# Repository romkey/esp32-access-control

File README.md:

# esp32-access-control

An open source, ESP32-based Wiegand reader: a board, ESPHome firmware and a 3D-printable case.

At PDX Hackerspace we used RFID keys to unlock doors and access our laser cutter. We want to expand their use, to make it easy for members to print parking permits for projects, unlock the main entrance for events, claim prints on 3D printers and more. We currently use Raspberry Pis for the doors and an ESPKey for the laser cutter; this project can provide a low cost simple way to integrate with Wiegand RFID readers and possibly as the basis for replacing the aging Raspberry Pis controlling our doors.

> **AI disclosure:** This project was written by AI under human oversight,
> following [these rules](https://github.com/romkey/esphome-ai-coding-rules/blob/main/RULES.md).

## What's here

| Path | What it is |
|------|------------|
| `hw/reader/<version>/` | KiCad project for the board, one directory per revision |
| `BOFFF.md` | Bill of Form, Fit and Function: board outline, mounting holes and connector positions, for designing enclosures |
| `examples/access-control.yaml` | The door controller: Wiegand reader, access database, door relay, syslog |
| `examples/simple.yaml` | ESPHome config for bring-up: LED switch, reader LED and beeper, Wiegand tag reading |
| `examples/common/base.yaml` | Settings every example shares: encrypted API and OTA, recovery, web server |
| `packages/` | Board-agnostic ESPHome packages for the door controller; pins come from the including config |
| `components/` | C++ external components: `access_db`, `access_site`, `access_syslog`, `push_auth` |
| `case/` | OpenSCAD design for a wall or desk kiosk in portrait and landscape layouts; see [case/README.md](case/README.md) |
| `datasheets/` | Manufacturer datasheets, each with a license note |
| `docs/` | [Overview](docs/overview.md) and [configuration reference](docs/configuration.md) |

## Technical details

Hardware:

- dual level-shifted 5V Wiegand interfaces with wiring for data (D0, D1), LED and beep along with power
- ESP32-S3-N16R8: ESP32-S3 with 16MB of flash and 8MB of octal PSRAM (GPIO35-37 are used by the PSRAM and unavailable)
- USB C port
- power and data LEDs
- Qwiic connector for I2C devices
- header for SPI TFT displays with touch controllers
- "aux" header for satellite boards with optional power to this board

Connectors, from [BOFFF.md](BOFFF.md):

| Ref | Part | What it is |
|-----|------|------------|
| J1 | 10-pin header | Aux: GND, 3.3V, TX0, RX0, IO42, IO41, IO40, IO39, IO38, +5V in |
| J2 | 14-pin header | SPI TFT with touch: 3.3V, GND, CS, RST, DC, SDO, SCK, LED, SDI, then T_CLK, T_CS, T_DIN, T_DO, T_IRQ |
| J3 | SM04B-SRSS-TB | Qwiic: GND, 3.3V, SDA, SCL |
| J4 | USB-C | Power and programming |
| J5, J6 | WAGO 2601-1106 | Wiegand readers 1 and 2: +5V, GND, then four signals (D0, D1, LED, beep; see the schematic for the order) |

I2C: SDA and SCL on J3, with 4.7k pull-ups to 3.3V. The board carries no I2C devices of its own.

`examples/simple.yaml` and `examples/access-control.yaml` wire one reader on D0 = GPIO18, D1 = GPIO17, reader LED = GPIO16
(active low) and beeper = GPIO15 (active low). Check these against the schematic before
relying on them. The board has no relay output; `packages/door-relays.yaml` is an example for a relay or strike driven from
the J1 aux header or a satellite board. `examples/access-control.yaml` uses GPIO38 and GPIO39 (J1) as example
values; set `door_relay_1_pin` and `door_relay_2_pin` for your own hardware.

Using the packages from another project:

```yaml
external_components:
  - source: github://romkey/esp32-access-control@vX.Y.Z
packages:
  access-door: github://romkey/esp32-access-control/packages/access-door.yaml@vX.Y.Z
```

See [docs/configuration.md](docs/configuration.md) for the substitutions each package takes.

Datasheets: [TXS0108E level shifter](datasheets/txs0108e.pdf),
[WAGO 2601-1106 terminal block](datasheets/2946_WAGO26011106enUS.pdf).

## Building

Requires Docker. Nothing else needs installing.

```bash
cp examples/secrets.yaml.example examples/secrets.yaml   # then edit it (generate a real api key)
docker compose run --rm validate      # esphome config on every example
docker compose run --rm build         # compile every example
docker compose run --rm lint          # all pre-commit checks, like CI
```

The first build downloads the toolchains into a Docker volume; later builds reuse
them and only recompile what changed.

The case is built separately with OpenSCAD: `make -C case`. See [case/README.md](case/README.md).

## Flashing

To flash a new board, build the firmware images:

```bash
docker compose run --rm firmware
```

Then open https://web.esphome.io in Chrome or Edge, connect the board over USB and upload
`dist/<name>.factory.bin`. After that, update over the network (OTA). The images contain
your Wi-Fi credentials; don't share them.

## Case

[`case/`](case/) has an OpenSCAD design for a 3D-printable wall or desk kiosk, in portrait and landscape layouts. It holds the board, a 3.5" or 4.0" SPI TFT, and an HID ProxPoint Plus reader mounted on the front. CI renders the STLs on every change and attaches them to the workflow run. See [`case/README.md`](case/README.md) for parts, print settings and assumptions to check.

## License

[MIT](LICENSE), except the manufacturer datasheets in [datasheets/](datasheets/),
which belong to their manufacturers and are not covered by this license; see
each datasheet's `-license.txt`.

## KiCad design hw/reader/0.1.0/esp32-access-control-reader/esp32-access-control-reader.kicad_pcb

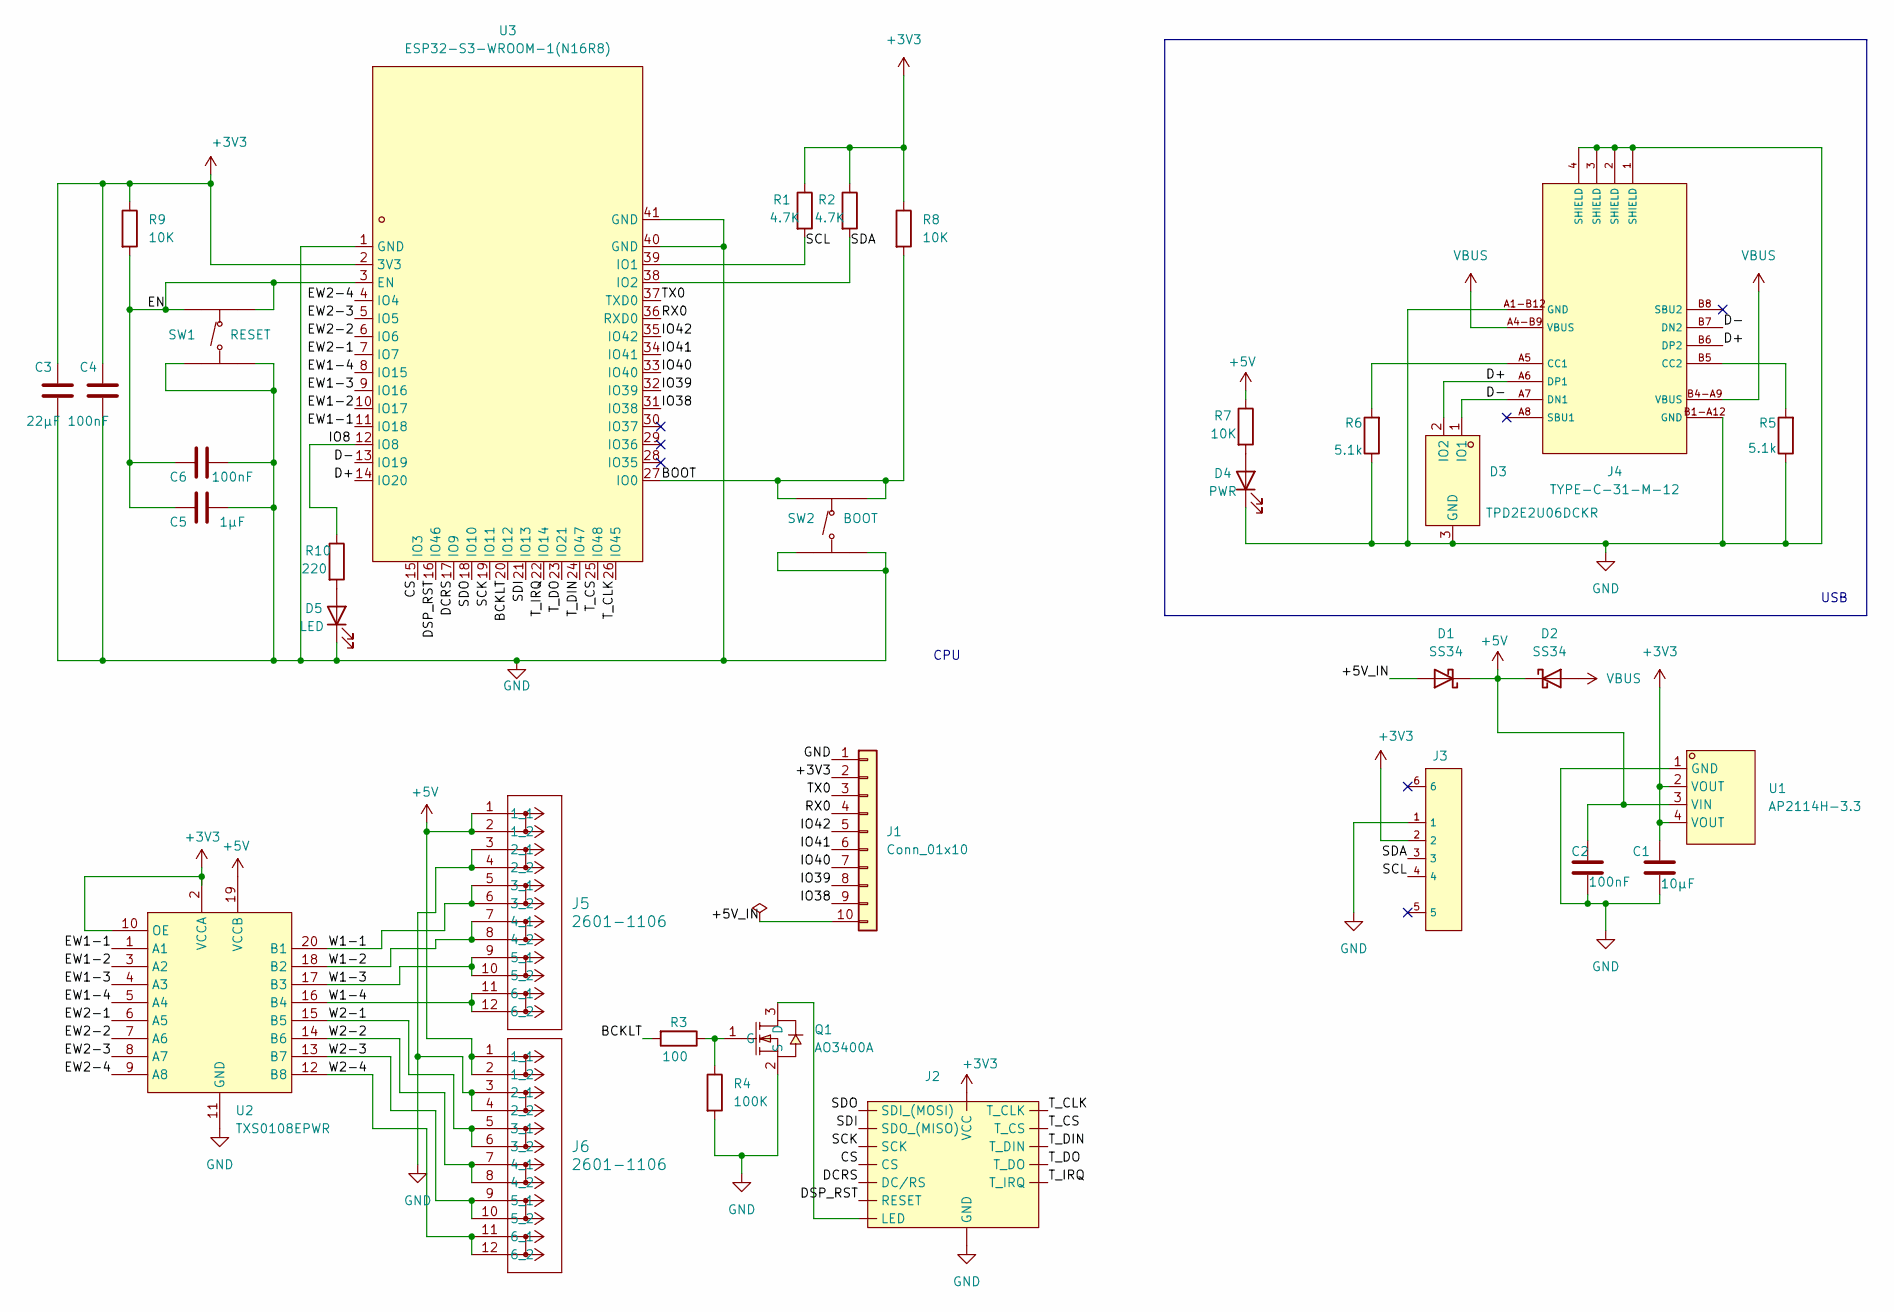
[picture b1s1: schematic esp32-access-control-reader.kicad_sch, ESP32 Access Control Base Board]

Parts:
C1: 10µF; C_0603_1608Metric; LCSC C19702
C2, C4, C6: 100nF; C_0603_1608Metric; LCSC C14663
C3: 22µF; C_0603_1608Metric; LCSC C59461
C5: 1µF; C_0603_1608Metric; LCSC C15849
D1, D2: SS34; D_SMA; LCSC Part C8678
D3: TPD2E2U06DCKR; SC-70-3_L2.0-W1.3-P0.65-LS2.1-BL; LCSC Part C1855726
D4: PWR; LED_0805_2012Metric; LCSC C84256
D5: LED; LED_0805_2012Metric; LCSC C2297
J1: Conn_01x10; PinHeader_1x10_P2.54mm_Vertical
J2: PinHeader_1x14_P2.54mm_Vertical
J3: SM04B-SRSS-TB_(LF)(SN); CONN-SMD_4P-P1.00_SM04B-SRSS-TB-LF-SN; LCSC C160404
J4: TYPE-C-31-M-12; USB-C-SMD_MC-311D; LCSC C136423
J5, J6: 2601-1106; CONN6_2601-1106_WAG
Q1: AO3400A; SOT-23-3_L2.9-W1.3-P1.90-LS2.4-BR; LCSC Part C20917
R1, R2: 4.7K; R_0603_1608Metric; LCSC C23162
R3: 100; R_0603_1608Metric; LCSC Part C22775
R4: 100K; R_0603_1608Metric; LCSC Part C25803
R5, R6: 5.1k; R_0603_1608Metric; LCSC C23186
R7, R8, R9: 10K; R_0603_1608Metric; LCSC C25804
R10: 220; R_0603_1608Metric; LCSC C22962
SW1: RESET; SW-SMD_4P-L5.1-W5.1-P3.70-LS6.5-TL_H1.5; LCSC C318884
SW2: BOOT; SW-SMD_4P-L5.1-W5.1-P3.70-LS6.5-TL_H1.5; LCSC C318884
U1: AP2114H-3.3; SOT-223_L6.7-W3.5-P2.30-BR; LCSC C150716
U2: TXS0108EPWR; TSSOP-20_L6.5-W4.4-P0.65-LS6.4-BL; LCSC Part C17206
U3: ESP32-S3-WROOM-1(N16R8); WIRELM-SMD_ESP32-S3-WROOM-1; LCSC Part C2913202

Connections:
+3V3: C1.1, C3.1, C4.1, J1.2, J2.1 (VCC), J3.2, R1.1, R2.1, R8.1, R9.1, U1.2 (VOUT), U1.4 (VOUT), U2.2 (VCCA), U2.10 (OE), U3.2 (3V3)
+5V: C2.1, D1.1 (K), D2.1 (K), J5.1 (1_1), J5.2 (1_2), J6.1 (1_1), J6.2 (1_2), R7.1, U1.3 (VIN), U2.19 (VCCB)
/+5V_IN: D1.2 (A), J1.10
/BCKLT: R3.2, U3.20 (IO12)
/BOOT: R8.2, SW2.1 (A), SW2.2 (B), U3.27 (IO0)
/CS: J2.3 (CS), U3.15 (IO3)
/D+: D3.2 (IO2), J4.A6 (DP1), J4.B6 (DP2), U3.14 (IO20)
/D-: D3.1 (IO1), J4.A7 (DN1), J4.B7 (DN2), U3.13 (IO19)
/DCRS: J2.5 (DC/RS), U3.17 (IO9)
/DSP_RST: J2.4 (RESET), U3.16 (IO46)
/EN: C5.1, C6.1, R9.2, SW1.1 (A), SW1.2 (B), U3.3 (EN)
/EW1-1: U2.1 (A1), U3.11 (IO18)
/EW1-2: U2.3 (A2), U3.10 (IO17)
/EW1-3: U2.4 (A3), U3.9 (IO16)
/EW1-4: U2.5 (A4), U3.8 (IO15)
/EW2-1: U2.6 (A5), U3.7 (IO7)
/EW2-2: U2.7 (A6), U3.6 (IO6)
/EW2-3: U2.8 (A7), U3.5 (IO5)
/EW2-4: U2.9 (A8), U3.4 (IO4)
/IO8: R10.1, U3.12 (IO8)
/IO38: J1.9, U3.31 (IO38)
/IO39: J1.8, U3.32 (IO39)
/IO40: J1.7, U3.33 (IO40)
/IO41: J1.6, U3.34 (IO41)
/IO42: J1.5, U3.35 (IO42)
/RX0: J1.4, U3.36 (RXD0)
/SCK: J2.7 (SCK), U3.19 (IO11)
/SCL: J3.4, R1.2, U3.39 (IO1)
/SDA: J3.3, R2.2, U3.38 (IO2)
/SDI: J2.9 (SDO_(MISO)), U3.21 (IO13)
/SDO: J2.6 (SDI_(MOSI)), U3.18 (IO10)
/TX0: J1.3, U3.37 (TXD0)
/T_CLK: J2.10 (T_CLK), U3.26 (IO45)
/T_CS: J2.11 (T_CS), U3.25 (IO48)
/T_DIN: J2.12 (T_DIN), U3.24 (IO47)
/T_DO: J2.13 (T_DO), U3.23 (IO21)
/T_IRQ: J2.14 (T_IRQ), U3.22 (IO14)
/W1-1: J5.5 (3_1), J5.6 (3_2), U2.20 (B1)
/W1-2: J5.7 (4_1), J5.8 (4_2), U2.18 (B2)
/W1-3: J5.9 (5_1), J5.10 (5_2), U2.17 (B3)
/W1-4: J5.11 (6_1), J5.12 (6_2), U2.16 (B4)
/W2-1: J6.5 (3_1), J6.6 (3_2), U2.15 (B5)
/W2-2: J6.7 (4_1), J6.8 (4_2), U2.14 (B6)
/W2-3: J6.9 (5_1), J6.10 (5_2), U2.13 (B7)
/W2-4: J6.11 (6_1), J6.12 (6_2), U2.12 (B8)
GND: C1.2, C2.2, C3.2, C4.2, C5.2, C6.2, D3.3 (GND), D4.1 (K), D5.1 (K), J1.1, J2.2 (GND), J3.1, J4.1 (SHIELD), J4.2 (SHIELD), J4.3 (SHIELD), J4.4 (SHIELD), J4.A1-B12 (GND), J4.B1-A12 (GND), J5.3 (2_1), J5.4 (2_2), J6.3 (2_1), J6.4 (2_2), Q1.2 (S), R4.2, R5.1, R6.1, SW1.3 (C), SW1.4 (D), SW2.3 (C), SW2.4 (D), U1.1 (GND), U2.11 (GND), U3.1 (GND), U3.40 (GND), U3.41 (GND)
unnamed: D4.2 (A), R7.2
unnamed: D5.2 (A), R10.2
unnamed: J2.8 (LED), Q1.3 (D)
unnamed: J4.A5 (CC1), R6.2
unnamed: J4.B5 (CC2), R5.2
unnamed: Q1.1 (G), R3.1, R4.1
VBUS: D2.2 (A), J4.A4-B9 (VBUS), J4.B4-A9 (VBUS)

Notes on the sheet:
CPU
USB

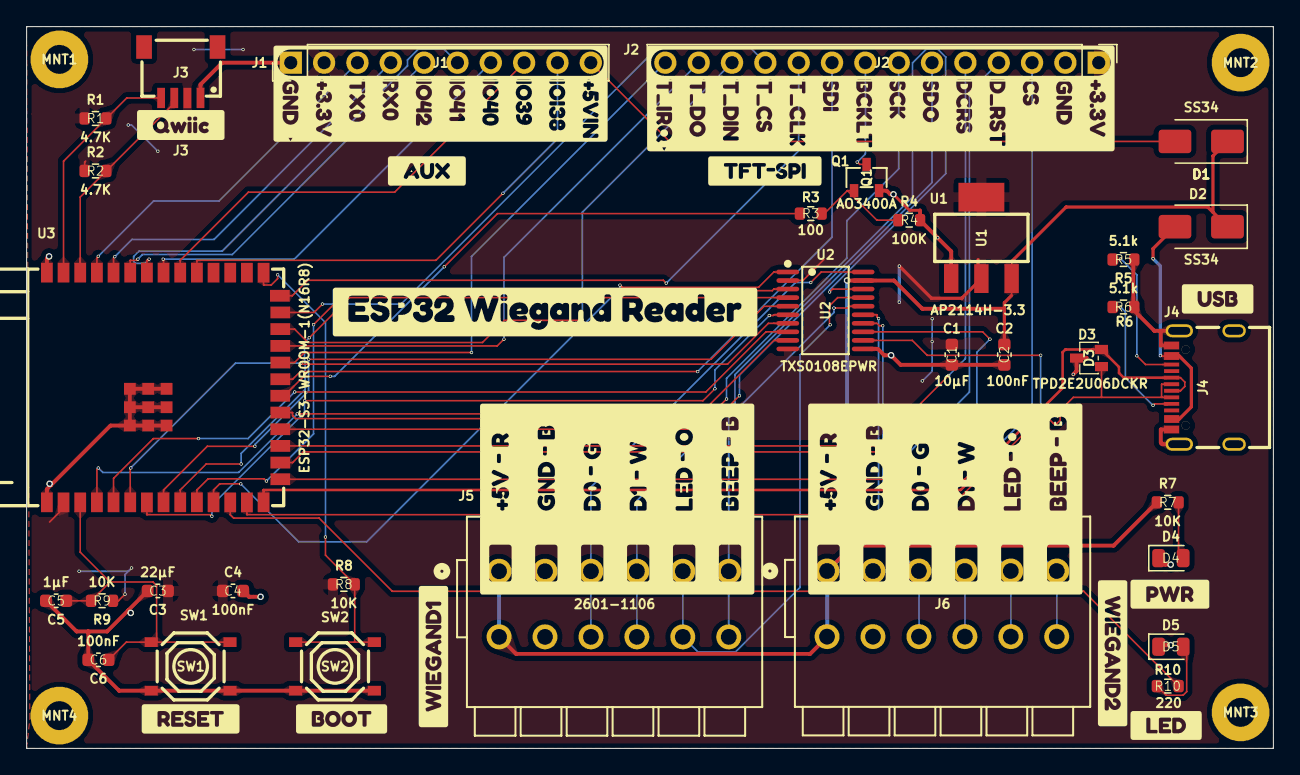
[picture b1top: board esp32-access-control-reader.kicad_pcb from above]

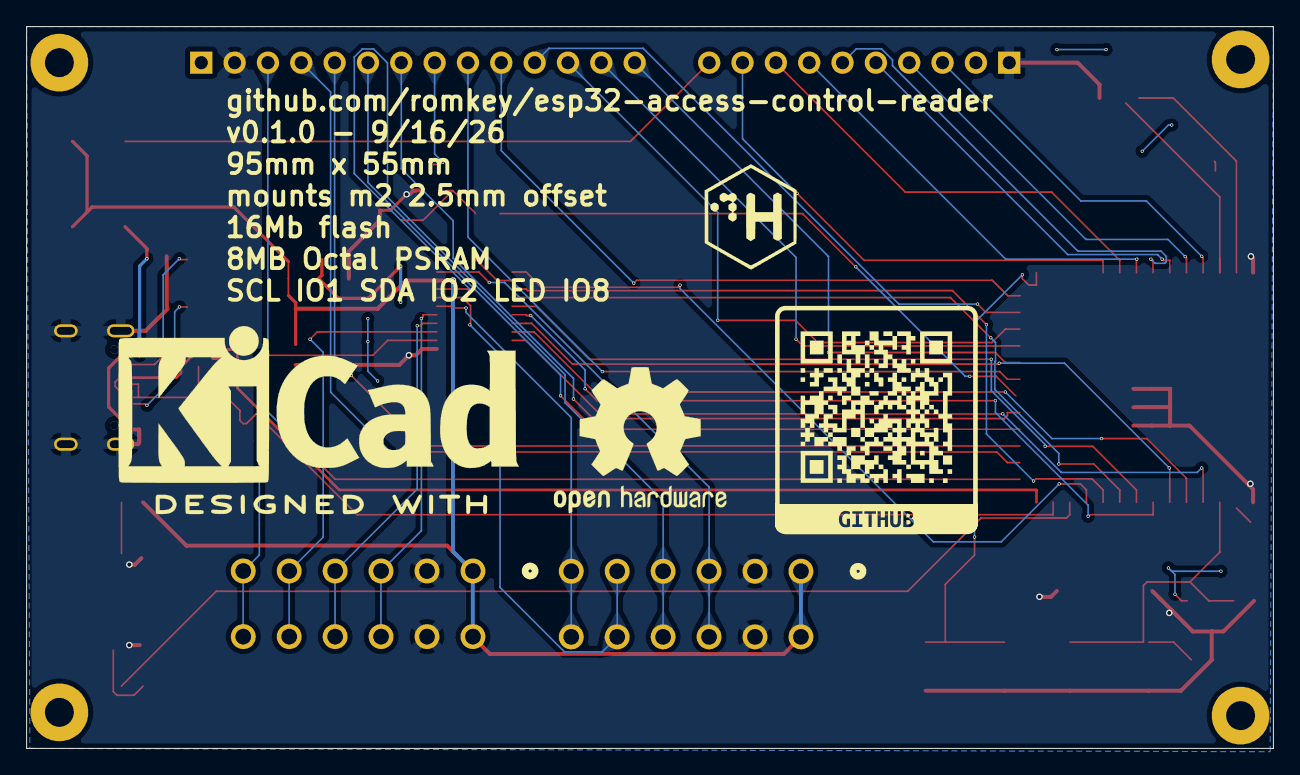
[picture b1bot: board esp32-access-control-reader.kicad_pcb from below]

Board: 2 copper layers, 95.0 x 55.0 mm, 54 parts (2 on the bottom side), 53 nets.

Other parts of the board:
MNT1, MNT2, MNT3, MNT4: MountingHole_2.2mm_M2_Pad
NOT2: CTRLH Logo
kobee-studio-1: G***; kobee-studio-6AA82569
kobee-studio-2: G***; kobee-studio-6AA4CD99
kobee-studio-3: G***; kobee-studio-6A958584
kobee-studio-4: G***; kobee-studio-6AA4CF77
kobee-studio-5: G***; kobee-studio-6AA4CF94
kobee-studio-6: G***; kobee-studio-6A95859C
kobee-studio-6AAB212F: G***; kobee-studio-6AAB212F
kobee-studio-7: G***; kobee-studio-6AA480A6
kobee-studio-8, kobee-studio-9: Kobee Studio; kobee-studio-6AA40528
kobee-studio-10: G***; kobee-studio-6AA432D5
kobee-studio-11: G***; kobee-studio-6AA2D906
kobee-studio-12: G***; kobee-studio-6AA2D8EB
kobee-studio-13: G***; kobee-studio-6A950CF3
kobee-studio-14: G***; kobee-studio-6A950CDA
kobee-studio-15: G***; kobee-studio-6AA432BC
